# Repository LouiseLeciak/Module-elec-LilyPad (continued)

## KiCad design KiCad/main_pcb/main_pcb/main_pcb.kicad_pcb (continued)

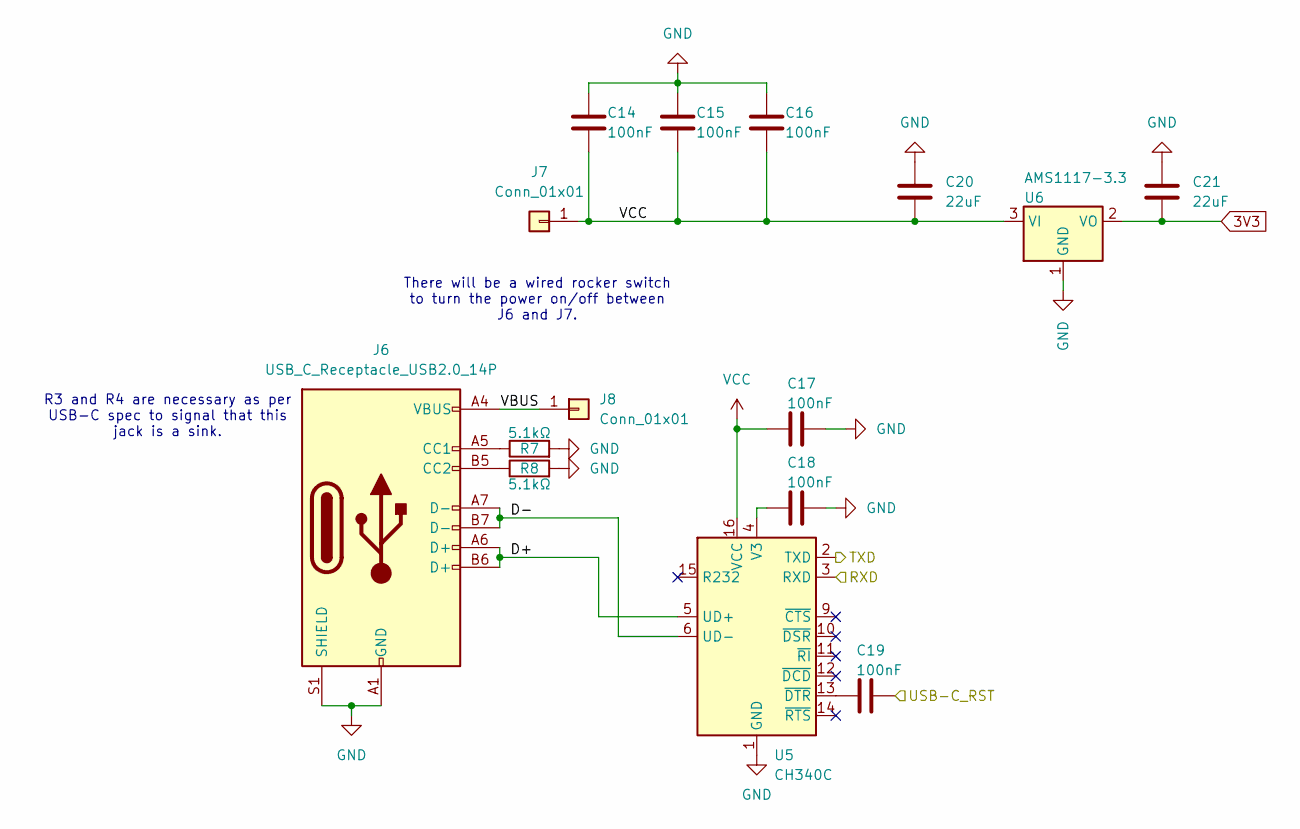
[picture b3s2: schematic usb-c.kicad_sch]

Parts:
C14, C15, C16, C17, C18, C19: 100nF; C_0603_1608Metric_Pad1.08x0.95mm_HandSolder
C20, C21: 22uF; C_0603_1608Metric_Pad1.08x0.95mm_HandSolder
J6: USB_C_Receptacle_USB2.0_14P; USB_C_Receptacle_HRO_TYPE-C-31-M-12
J7, J8: Conn_01x01; PinHeader_1x01_P2.54mm_Vertical
R7, R8: 5.1kΩ; R_0603_1608Metric_Pad0.98x0.95mm_HandSolder
U5: CH340C; SOIC-16_3.9x9.9mm_P1.27mm
U6: AMS1117-3.3; SOT-223-3_TabPin2

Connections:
3V3: C21.2, U6.2 (VO); also elsewhere on the board
/USB-C/D+: J6.A6 (D+), J6.B6 (D+), U5.5 (UD+)
/USB-C/D-: J6.A7 (D-), J6.B7 (D-), U5.6 (UD-)
/USB-C/RXD: U5.3 (RXD); also elsewhere on the board
/USB-C/TXD: U5.2 (TXD); also elsewhere on the board
/USB-C/USB-C_RST: C19.2; also elsewhere on the board
/USB-C/VBUS: J6.A4 (VBUS), J6.A9 (VBUS), J6.B4 (VBUS), J6.B9 (VBUS), J8.1
GND: C14.1, C15.1, C16.1, C17.2, C18.2, C20.1, C21.1, J6.A1 (GND), J6.A12 (GND), J6.B1 (GND), J6.B12 (GND), J6.S1 (SHIELD), R7.2, R8.2, U5.1 (GND), U6.1 (GND); also elsewhere on the board
unnamed: J6.A5 (CC1), R7.1
unnamed: J6.B5 (CC2), R8.1
unnamed: C18.1, U5.4 (V3)
unnamed: C19.1, U5.13 (~DTR)
VCC: C14.2, C15.2, C16.2, C17.1, C20.2, J7.1, U5.16 (VCC), U6.3 (VI); also elsewhere on the board

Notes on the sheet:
R3 and R4 are necessary as per USB-C spec to signal that this jack is a sink.
There will be a wired rocker switch to turn the power on/off between J6 and J7.

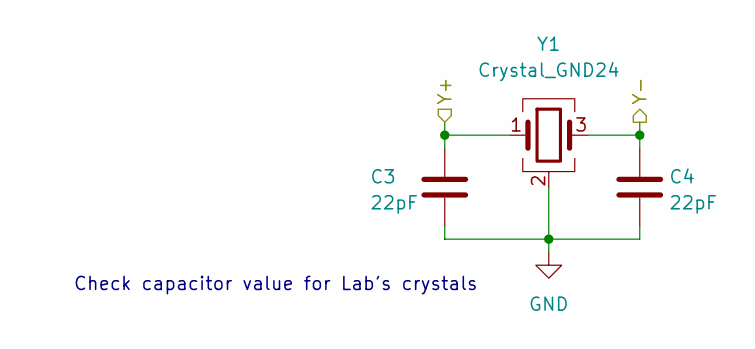
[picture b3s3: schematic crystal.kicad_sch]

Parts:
C3, C4: 22pF; C_0603_1608Metric_Pad1.08x0.95mm_HandSolder
Y1: Crystal_GND24; Crystal_SMD_3225-4Pin_3.2x2.5mm_HandSoldering

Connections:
/Y+: C3.2, Y1.1; also elsewhere on the board
/Y-: C4.2, Y1.3; also elsewhere on the board
GND: C3.1, C4.1, Y1.2 (G), Y1.4 (G); also elsewhere on the board

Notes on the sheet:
Check capacitor value for Lab's crystals

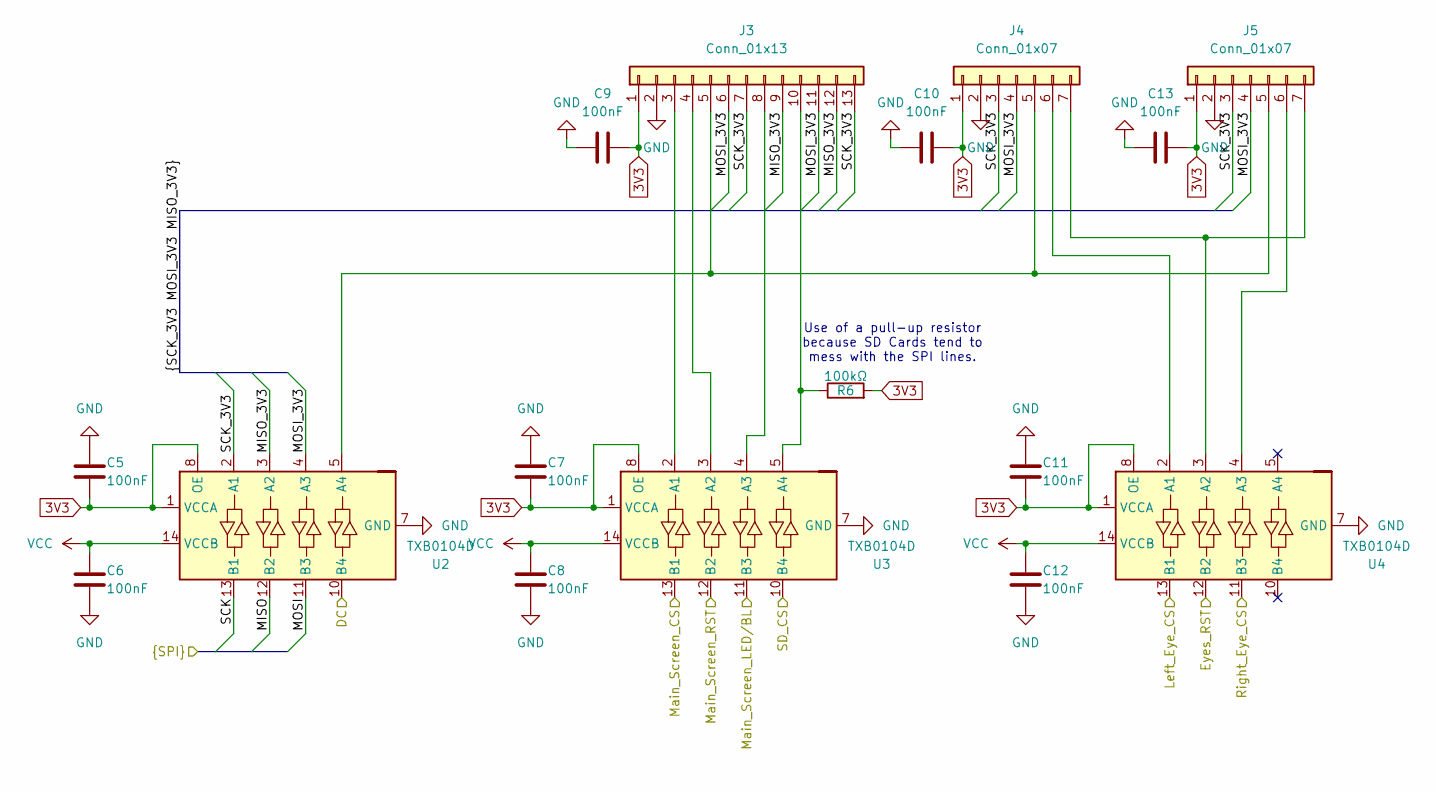
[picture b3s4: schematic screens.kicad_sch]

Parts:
C5, C6, C7, C8, C9, C10, C11, C12, C13: 100nF; C_0603_1608Metric_Pad1.08x0.95mm_HandSolder
J3: Conn_01x13; PinHeader_1x13_P2.54mm_Vertical
J4, J5: Conn_01x07; PinHeader_1x07_P2.54mm_Vertical
R6: 100kΩ; R_0603_1608Metric_Pad0.98x0.95mm_HandSolder
U2, U3, U4: TXB0104D; SOIC-14_3.9x8.7mm_P1.27mm

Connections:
3V3: C5.2, C7.2, C9.2, C10.2, C11.2, C13.2, J3.1, J4.1, J5.1, R6.2, U2.1 (VCCA), U2.8 (OE), U3.1 (VCCA), U3.8 (OE), U4.1 (VCCA), U4.8 (OE); also elsewhere on the board
/MISO: U2.12 (B2); also elsewhere on the board
/MOSI: U2.11 (B3); also elsewhere on the board
/SCK: U2.13 (B1); also elsewhere on the board
/Screens/DC: U2.10 (B4); also elsewhere on the board
/Screens/Eyes_RST: U4.12 (B2); also elsewhere on the board
/Screens/Left_Eye_CS: U4.13 (B1); also elsewhere on the board
/Screens/MISO_3V3: J3.9, J3.12, U2.3 (A2)
/Screens/MOSI_3V3: J3.6, J3.11, J4.4, J5.4, U2.4 (A3)
/Screens/Main_Screen_CS: U3.13 (B1); also elsewhere on the board
/Screens/Main_Screen_LED/BL: U3.11 (B3); also elsewhere on the board
/Screens/Main_Screen_RST: U3.12 (B2); also elsewhere on the board
/Screens/Right_Eye_CS: U4.11 (B3); also elsewhere on the board
/Screens/SCK_3V3: J3.7, J3.13, J4.3, J5.3, U2.2 (A1)
/Screens/SD_CS: U3.10 (B4); also elsewhere on the board
GND: C5.1, C6.1, C7.1, C8.1, C9.1, C10.1, C11.1, C12.1, C13.1, J3.2, J4.2, J5.2, U2.7 (GND), U3.7 (GND), U4.7 (GND); also elsewhere on the board
unnamed: J3.3, U3.2 (A1)
unnamed: J3.4, U3.3 (A2)
unnamed: J3.5, J4.5, J5.5, U2.5 (A4)
unnamed: J3.8, U3.4 (A3)
unnamed: J3.10, R6.1, U3.5 (A4)
unnamed: J4.6, U4.2 (A1)
unnamed: J4.7, J5.7, U4.3 (A2)
unnamed: J5.6, U4.4 (A3)
VCC: C6.2, C8.2, C12.2, U2.14 (VCCB), U3.14 (VCCB), U4.14 (VCCB); also elsewhere on the board

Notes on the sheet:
Use of a pull-up resistor because SD Cards tend to mess with the SPI lines.

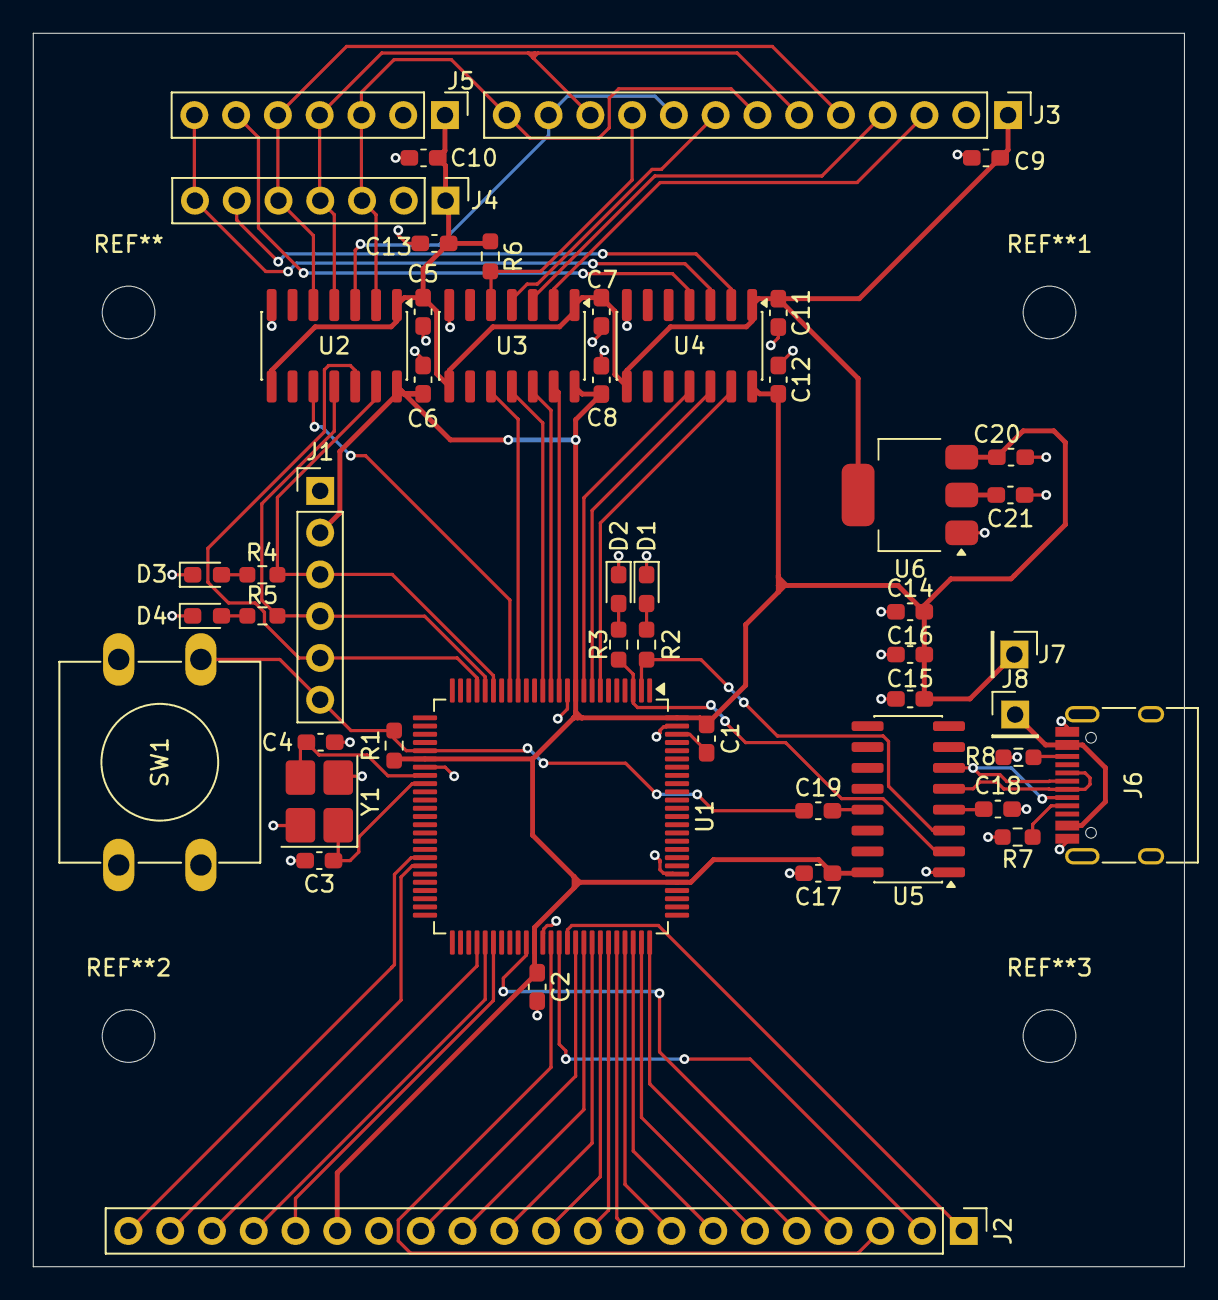
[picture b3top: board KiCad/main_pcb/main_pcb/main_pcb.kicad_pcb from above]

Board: 2 copper layers, 70.0 x 75.0 mm, 49 parts (0 on the bottom side), 61 nets.

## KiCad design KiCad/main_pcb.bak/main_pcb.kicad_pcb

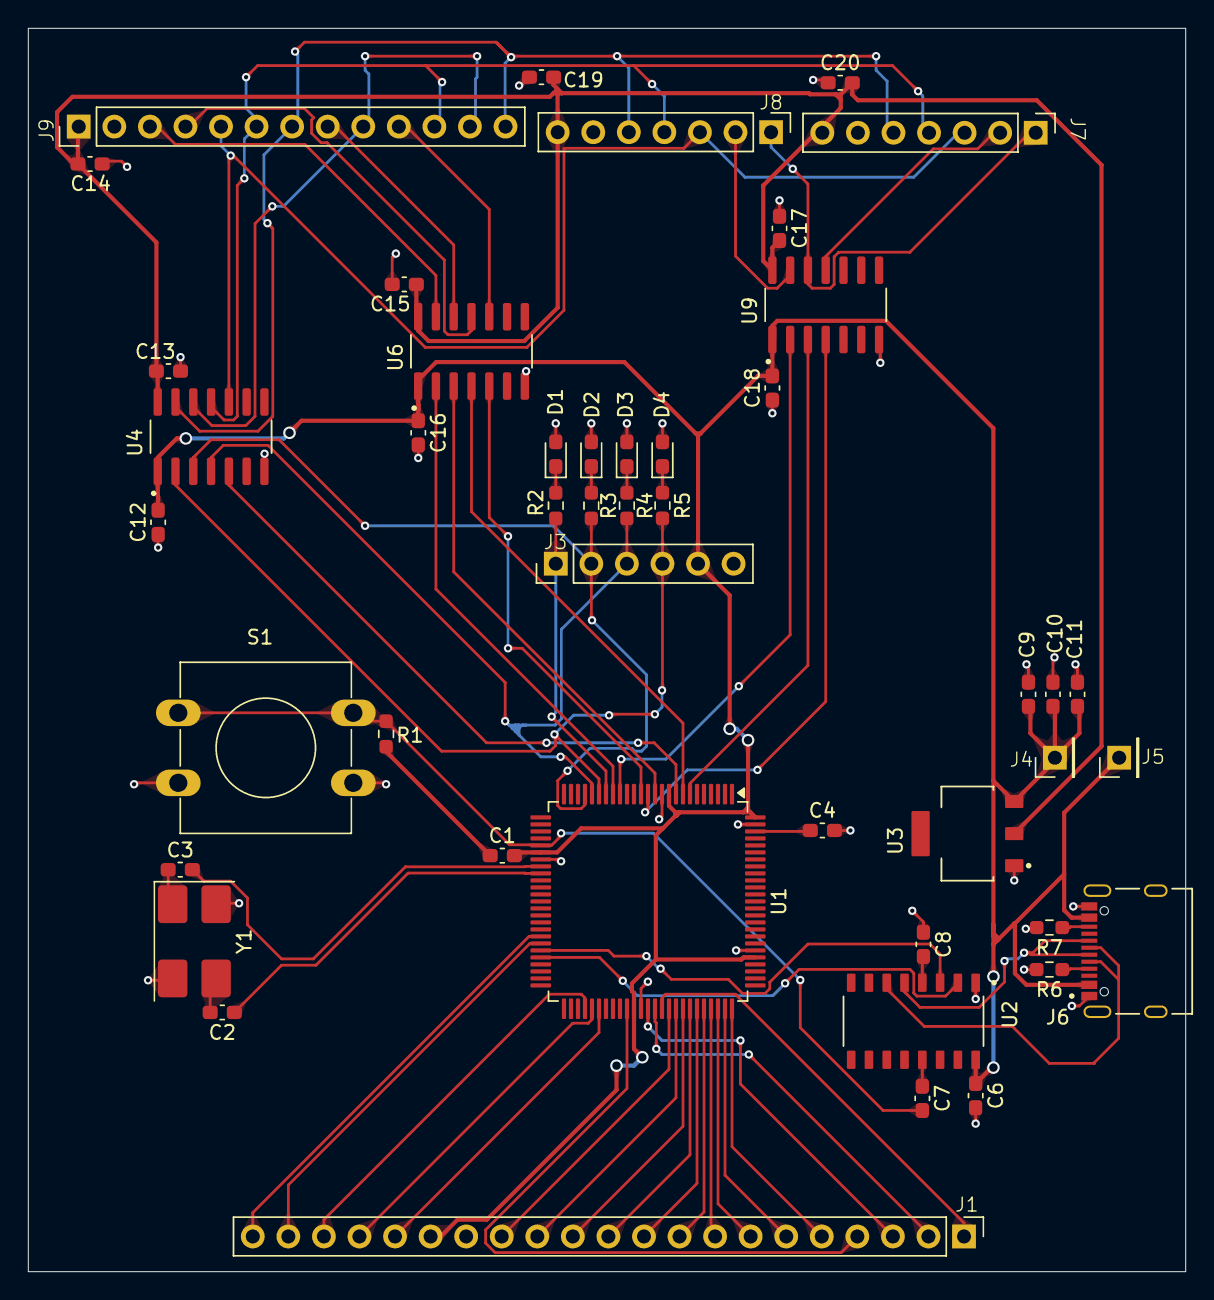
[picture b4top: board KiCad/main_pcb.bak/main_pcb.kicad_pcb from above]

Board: 2 copper layers, 82.7 x 88.8 mm, 46 parts (0 on the bottom side), 59 nets.

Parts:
C1, C4, C6, C7, C8, C12, C13, C14, C15, C16, C17, C18, C19, C20: 100nF; C_0603_1608Metric_Pad1.08x0.95mm_HandSolder
C2, C3: 27pF; C_0603_1608Metric_Pad1.08x0.95mm_HandSolder
C9: 10uF; C_0603_1608Metric_Pad1.08x0.95mm_HandSolder
C10, C11: 0.1uF; C_0603_1608Metric_Pad1.08x0.95mm_HandSolder
D1, D2, D3, D4: LED_0603_1608Metric_Pad1.05x0.95mm_HandSolder
J1: 1x21 Header
J3: 1x6 Header
J4, J5: 1x1 Header
J6: TYPE-C-31-M-12; HRO_TYPE-C-31-M-12
J7, J8: 1X7 Header; 1x7 Header
J9: 1x13 Header
R1: 10kΩ; R_0603_1608Metric_Pad0.98x0.95mm_HandSolder
R2, R3, R4, R5: 330Ω; R_0603_1608Metric_Pad0.98x0.95mm_HandSolder
R6, R7: 5.1kΩ; R_0603_1608Metric_Pad0.98x0.95mm_HandSolder
S1: SW_PUSH-12mm
U1: ATmega 2560; TQFP-100_14x14mm_P0.5mm
U2: CH340C; SOIC127P600X180-16N
U3: JSMSEMI AMS1117-3.3V; SOT229P700X180-4N
U4, U6, U9: TI TXB0104DR; SOIC127P600X175-14N
Y1: Crystal_SMD_0603-4Pin_6.0x3.5mm_HandSoldering

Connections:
3V3: C13.2, C14.1, C15.1, C17.2, C19.1, C20.2, J7.7, J8.7, J9.1, U3.2 (V_{OUT}), U4.14 (V_{CCB}), U6.14 (V_{CCB}), U9.14 (V_{CCB})
/C1: J1.5, U1.75 (PA3)
/C2: J1.6, U1.74 (PA4)
/C3: J1.7, U1.73 (PA5)
/C4: J1.8, U1.72 (PA6)
/C5: J1.9, U1.71 (PA7)
/C6: J1.10, U1.70 (PG2)
/C7: J1.11, U1.69 (PJ6)
/C8: J1.12, U1.68 (PJ5)
/C9: J1.13, U1.67 (PJ4)
/C10: J1.14, U1.66 (PJ3)
/D/C: J7.3, J8.3, J9.5, U1.9 (PE7), U4.5 (A4), U4.10 (B4)
/MISO: J3.2, J9.9, J9.12, R3.2, U1.22 (PB3), U4.3 (A2), U4.12 (B2)
/MOSI: J3.3, J7.4, J8.4, J9.6, J9.11, R4.2, U1.21 (PB2), U4.4 (A3), U4.11 (B3)
/Power and UART/UART_RX: U1.45 (PD2), U2.3 (RXD)
/Power and UART/UART_TX: U1.46 (PD3), U2.2 (TXD)
/R1: J1.1, U1.65 (PJ2)
/R2: J1.2, U1.64 (PJ1)
/R3: J1.3, U1.63 (PJ0)
/R4: J1.4, U1.60 (PC7)
/SCK: J3.4, J7.5, J8.5, J9.7, J9.13, R5.2, U1.20 (PB1), U4.2 (A1), U4.13 (B1)
/SCL: J1.21, U1.43 (PD0)
/SDA: J1.20, U1.44 (PD1)
/SLD_SW1: J1.19, U1.54 (PC1)
/SLD_SW2: J1.18, U1.55 (PC2)
/SLD_SW3: J1.17, U1.56 (PC3)
/SS: J3.1, R2.2, U1.19 (PB0)
/Y+: C3.1, U1.33 (XTAL2)
/Y-: C2.1, U1.34 (XTAL1)
/screens/CS Left Eye: U1.17 (PH5), U9.2 (A1)
/screens/CS Main Screen: U1.18 (PH6), U6.2 (A1)
/screens/CS Main Screen 3V3: J9.3, U6.13 (B1)
/screens/CS Right Eye: U1.13 (PH1), U9.4 (A3)
/screens/CS SD: U1.14 (PH2), U6.5 (A4)
/screens/LED/BL: U1.12 (PH0), U6.3 (A2)
/screens/RST Eyes: U1.7 (PE5), U9.3 (A2)
/screens/RST Main Screen: U1.8 (PE6), U6.4 (A3)
GND: C4.2, C6.2, C8.1, C9.2, C10.2, C11.2, C12.1, C13.1, C14.2, C15.2, C16.2, C17.1, C18.1, C19.2, C20.1, D1.2, D2.2, D3.2, D4.2, J1.15, J3.6, J6.A1_B12 (GND), J6.B1_A12 (GND), J6.S1 (SHIELD), J6.S2 (SHIELD), J6.S3 (SHIELD), J6.S4 (SHIELD), J7.6, J8.6, J9.2, R6.2, R7.2, S1.2, U1.11 (GND), U1.32 (GND), U1.62 (GND), U1.81 (GND), U1.99 (GND), U2.1 (GND), U3.1 (V_{SS}), U4.7 (GND), U6.7 (GND), U9.7 (GND), Y1.2 (G), Y1.4 (G)
unnamed: C2.2, Y1.3
unnamed: C3.2, Y1.1
unnamed: D1.1, R2.1
unnamed: D2.1, R3.1
unnamed: D3.1, R4.1
unnamed: D4.1, R5.1
unnamed: J6.A5 (CC1), R6.1
unnamed: J6.B5 (CC2), R7.1
unnamed: J6.A7 (DN1), J6.B7 (DN2), U2.6 (UD-)
unnamed: J6.A6 (DP1), J6.B6 (DP2), U2.5 (UD+)
unnamed: C4.1, U1.98 (AREF)
unnamed: C7.1, U2.13 (DTR#)
unnamed: C8.2, U2.4 (V3)
unnamed: J9.8, U6.12 (B2)
unnamed: J9.4, U6.11 (B3)
unnamed: J9.10, U6.10 (B4)
unnamed: J8.2, U9.13 (B1)
unnamed: J7.1, J8.1, U9.12 (B2)
unnamed: J7.2, U9.11 (B3)
VCC: C1.1, C1.2, C6.1, C9.1, C10.1, C11.1, C12.2, C16.1, C18.2, J1.16, J3.5, J4.1, J5.1, J6.A4_B9 (VBUS), J6.B4_A9 (VBUS), R1.1, U1.10 (VCC), U1.31 (VCC), U1.61 (VCC), U1.80 (VCC), U1.100 (AVCC), U2.16 (VCC), U3.3 (V_{IN}), U4.1 (V_{CCA}), U6.1 (V_{CCA}), U9.1 (V_{CCA})
uC_Reset: C7.2, R1.2, S1.1, U1.30 (~RESET)

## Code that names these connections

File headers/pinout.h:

#ifndef PINOUT_H
#define PINOUT_H

// I2C GENERAL
#define SCL (1 << PD0)
#define SDA (1 << PD1)

// SPI GENERAL
#define CS (1 << PB0)
#define SCK (1 << PB1)
#define MOSI (1 << PB2)
#define MISO (1 << PB3)

// SLAVE SELECTS (SPI)
#define MAIN_SCREEN_CS (1 << PH0)
#define LEFT_EYE_CS (1 << PE5)
#define RIGHT_EYE_CS (1 << PE7)
#define SD_CS (1 << PH5)

// RESETS (SPI)
#define EYES_RST (1 << PE6)
#define MAIN_SCREEN_RST (1 << PH1)

// SCREENS SPI GENERAL
#define SCREENS_DC (1 << PH6)

// MAIN SCREEN SPI
#define MAIN_SCREEN_BL (1 << PH2)

// KEYBOARD
#define KB_R1 (1 << PJ2)
#define KB_R2 (1 << PJ1)
#define KB_R3 (1 << PJ0)
#define KB_R4 (1 << PC7)

#define KB_C1 (1 << PA3)
#define KB_C2 (1 << PA4)
#define KB_C3 (1 << PA5)
#define KB_C4 (1 << PA6)
#define KB_C5 (1 << PA7)
#define KB_C6 (1 << PG2)
#define KB_C7 (1 << PJ6)
#define KB_C8 (1 << PJ5)
#define KB_C9 (1 << PJ4)
#define KB_C10 (1 << PJ3)

// ROTARY ENCODER
#define SDL_SW1 (1 << PC1)
#define SDL_SW2 (1 << PC2)
#define SDL_SW3 (1 << PC3)

#define SD_CS_LOW() (PORTH &= ~(SD_CS))
#define SD_CS_HIGH() (PORTH |= (SD_CS))

#endif /* ifndef PINOUT_H */

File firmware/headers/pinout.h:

#ifndef PINOUT_H
#define PINOUT_H

// I2C GENERAL
#define SCL (1 << PD0)
#define SDA (1 << PD1)

// SPI GENERAL
#define CS (1 << PB0)
#define SCK (1 << PB1)
#define MOSI (1 << PB2)
#define MISO (1 << PB3)

// SLAVE SELECTS (SPI)
#define MAIN_SCREEN_CS (1 << PE4)
#define LEFT_EYE_CS (1 << PH4)
#define RIGHT_EYE_CS (1 << PH3)
#define SD_CS (1 << PE7)

// RESETS (SPI)
#define EYES_RST (1 << PH5)
#define MAIN_SCREEN_RST (1 << PE5)

// SCREENS SPI GENERAL
#define SCREENS_DC (1 << PH6)

// MAIN SCREEN SPI
#define MAIN_SCREEN_BL (1 << PE6)

// KEYBOARD
#define KB_R1 (1 << PC0)
#define KB_R2 (1 << PC1)
#define KB_R3 (1 << PC2)
#define KB_R4 (1 << PC3)

#define KB_C1 (1 << PC4)
#define KB_C2 (1 << PC5)
#define KB_C3 (1 << PC6)
#define KB_C4 (1 << PC7)
#define KB_C5 (1 << PJ0)
#define KB_C6 (1 << PJ1)
#define KB_C7 (1 << PJ2)
#define KB_C8 (1 << PJ3)
#define KB_C9 (1 << PJ4)
#define KB_C10 (1 << PJ5)

// ROTARY ENCODER
#define SDL_SW1 (1 << PJ6)
#define SDL_SW2 (1 << PG2)
#define SDL_SW3 (1 << PA7)

#define MAIN_SCREEN_CS_LOW() (PORTE &= ~(MAIN_SCREEN_CS))
#define MAIN_SCREEN_CS_HIGH() (PORTE |= (MAIN_SCREEN_CS))
#define SD_CS_LOW() (PORTE &= ~(SD_CS))
#define SD_CS_HIGH() (PORTE |= (SD_CS))
#define LEFT_EYE_CS_LOW() (PORTH &= ~(LEFT_EYE_CS))
#define LEFT_EYE_CS_HIGH() (PORTH |= (LEFT_EYE_CS))
#define RIGHT_EYE_CS_LOW() (PORTH &= ~(RIGHT_EYE_CS))
#define RIGHT_EYE_CS_HIGH() (PORTH |= (RIGHT_EYE_CS))

#define EYES_RST_LOW() (PORTH &= ~(EYES_RST))
#define EYES_RST_HIGH() (PORTH |= (EYES_RST))

#define MAIN_SCREEN_RST_HIGH() (PORTE |= (MAIN_SCREEN_RST))
#define MAIN_SCREEN_RST_LOW() (PORTE &= ~(MAIN_SCREEN_RST))
#define MAIN_SCREEN_BL_HIGH() (PORTE |= (MAIN_SCREEN_BL))
#define MAIN_SCREEN_BL_LOW() (PORTE &= ~(MAIN_SCREEN_BL))

#define DC_CMD() (PORTH &= ~(SCREENS_DC))
#define DC_DATA() (PORTH |= (SCREENS_DC))

#endif /* ifndef PINOUT_H */
